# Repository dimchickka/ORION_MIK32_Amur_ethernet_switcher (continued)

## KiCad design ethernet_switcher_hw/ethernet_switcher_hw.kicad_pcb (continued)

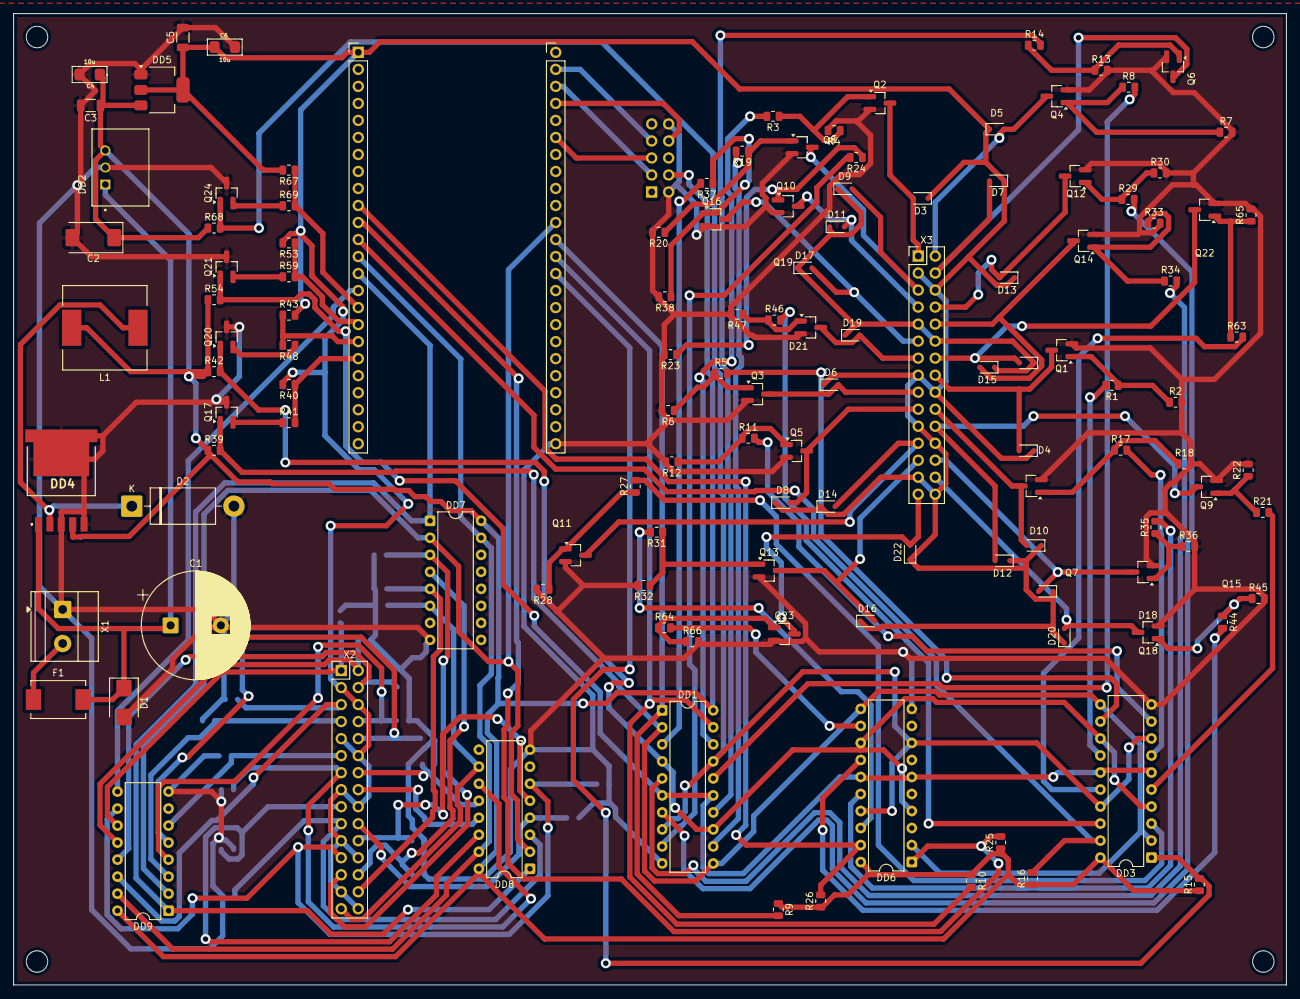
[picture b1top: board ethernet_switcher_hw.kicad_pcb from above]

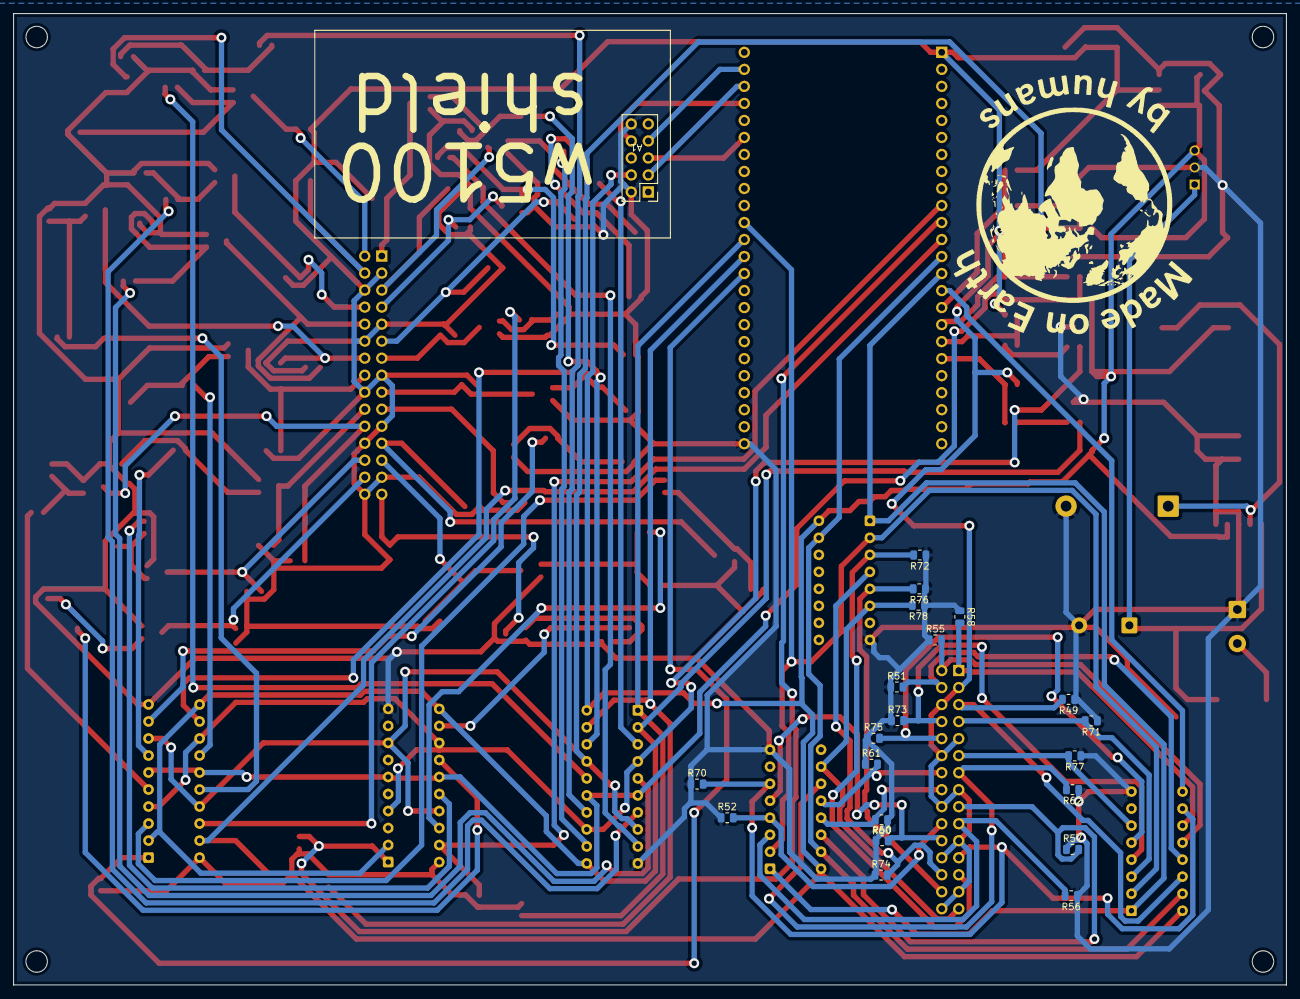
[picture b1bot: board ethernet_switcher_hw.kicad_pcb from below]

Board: 2 copper layers, 190.0 x 145.0 mm, 150 parts (21 on the bottom side), 112 nets.

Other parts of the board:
H1, H2, H3, H4: MountingHole_3.2mm_M3
